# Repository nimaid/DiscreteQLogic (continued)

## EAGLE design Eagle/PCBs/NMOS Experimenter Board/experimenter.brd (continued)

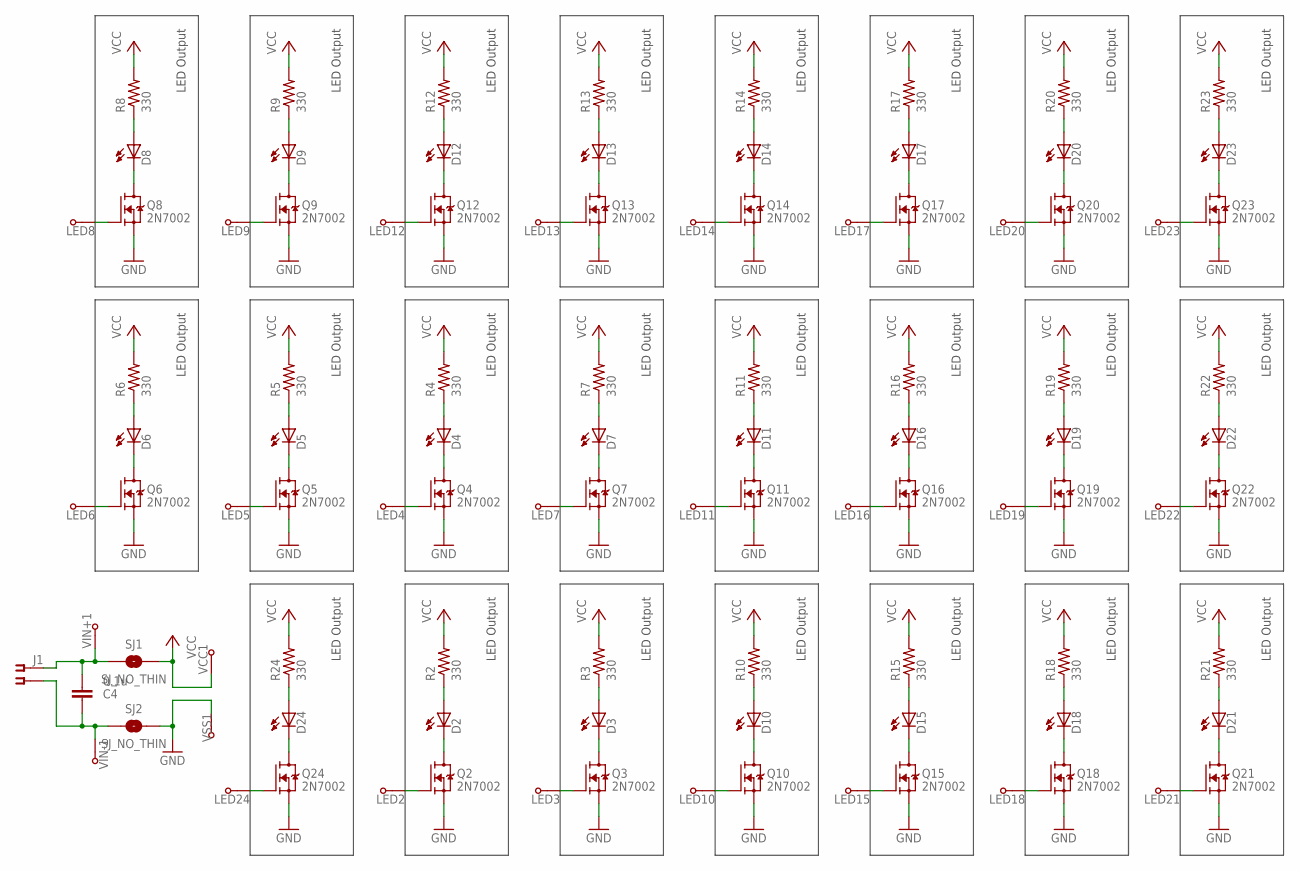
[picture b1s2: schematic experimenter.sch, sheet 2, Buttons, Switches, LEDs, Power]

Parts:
C4: 0.1u; C0603
D2, D3, D4, D5, D6, D7, D8, D9, D10, D11, D12, D13, D14, D15, D16, D17, D18, D19, D20, D21, D22, D23, D24: LED0603; CHIP-LED0603
J1: CON-F-2SCREWTERM-0.1"; OSTVN02A150
LED2, LED3, LED4, LED5, LED6, LED7, LED8, LED9, LED10, LED11, LED12, LED13, LED14, LED15, LED16, LED17, LED18, LED19, LED20, LED21, LED22, LED23, LED24: TPTHT; PROTOPAD-THT-PAD
Q2, Q3, Q4, Q5, Q6, Q7, Q8, Q9, Q10, Q11, Q12, Q13, Q14, Q15, Q16, Q17, Q18, Q19, Q20, Q21, Q22, Q23, Q24: 2N7002; SOT23
R2, R3, R4, R5, R6, R7, R8, R9, R10, R11, R12, R13, R14, R15, R16, R17, R18, R19, R20, R21, R22, R23, R24: 330; R0603
SJ1, SJ2: SJ_NO_THIN; SJ_2S-NO-THIN
VCC1: TPTHT; PROTOPAD-THT-PAD
VIN+1: TPTHT; PROTOPAD-THT-PAD
VIN-1: TPTHT; PROTOPAD-THT-PAD
VSS1: TPTHT; PROTOPAD-THT-PAD

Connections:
GND: Q2.2 (S), Q3.2 (S), Q4.2 (S), Q5.2 (S), Q6.2 (S), Q7.2 (S), Q8.2 (S), Q9.2 (S), Q10.2 (S), Q11.2 (S), Q12.2 (S), Q13.2 (S), Q14.2 (S), Q15.2 (S), Q16.2 (S), Q17.2 (S), Q18.2 (S), Q19.2 (S), Q20.2 (S), Q21.2 (S), Q22.2 (S), Q23.2 (S), Q24.2 (S), SJ2.2, VSS1.P1; also elsewhere on the board
unnamed: D10.A, R10.1
unnamed: LED10.P1, Q10.1 (G)
unnamed: D2.A, R2.1
unnamed: D10.C (K), Q10.3 (D)
unnamed: LED2.P1, Q2.1 (G)
unnamed: D2.C (K), Q2.3 (D)
unnamed: D3.A, R3.1
unnamed: LED3.P1, Q3.1 (G)
unnamed: D3.C (K), Q3.3 (D)
unnamed: D4.A, R4.1
unnamed: LED4.P1, Q4.1 (G)
unnamed: D4.C (K), Q4.3 (D)
unnamed: D5.A, R5.1
unnamed: LED5.P1, Q5.1 (G)
unnamed: D5.C (K), Q5.3 (D)
unnamed: D6.A, R6.1
unnamed: LED6.P1, Q6.1 (G)
unnamed: D6.C (K), Q6.3 (D)
unnamed: D7.A, R7.1
unnamed: LED7.P1, Q7.1 (G)
unnamed: D7.C (K), Q7.3 (D)
unnamed: D8.A, R8.1
unnamed: LED8.P1, Q8.1 (G)
unnamed: D8.C (K), Q8.3 (D)
unnamed: D9.A, R9.1
unnamed: LED9.P1, Q9.1 (G)
unnamed: D9.C (K), Q9.3 (D)
unnamed: D11.A, R11.1
unnamed: LED11.P1, Q11.1 (G)
unnamed: D11.C (K), Q11.3 (D)
unnamed: D12.A, R12.1
unnamed: LED12.P1, Q12.1 (G)
unnamed: D12.C (K), Q12.3 (D)
unnamed: D13.A, R13.1
unnamed: LED13.P1, Q13.1 (G)
unnamed: D13.C (K), Q13.3 (D)
unnamed: D14.A, R14.1
unnamed: LED14.P1, Q14.1 (G)
unnamed: D14.C (K), Q14.3 (D)
unnamed: D15.A, R15.1
unnamed: LED15.P1, Q15.1 (G)
unnamed: D15.C (K), Q15.3 (D)
unnamed: D16.A, R16.1
unnamed: LED16.P1, Q16.1 (G)
unnamed: D16.C (K), Q16.3 (D)
unnamed: D17.A, R17.1
unnamed: LED17.P1, Q17.1 (G)
unnamed: D17.C (K), Q17.3 (D)
unnamed: D18.A, R18.1
unnamed: LED18.P1, Q18.1 (G)
unnamed: D18.C (K), Q18.3 (D)
unnamed: D19.A, R19.1
unnamed: LED19.P1, Q19.1 (G)
unnamed: D19.C (K), Q19.3 (D)
unnamed: D20.A, R20.1
unnamed: LED20.P1, Q20.1 (G)
unnamed: D20.C (K), Q20.3 (D)
unnamed: D21.A, R21.1
unnamed: LED21.P1, Q21.1 (G)
unnamed: D21.C (K), Q21.3 (D)
unnamed: D22.A, R22.1
unnamed: LED22.P1, Q22.1 (G)
unnamed: D22.C (K), Q22.3 (D)
unnamed: D23.A, R23.1
unnamed: LED23.P1, Q23.1 (G)
unnamed: D23.C (K), Q23.3 (D)
unnamed: D24.A, R24.1
unnamed: LED24.P1, Q24.1 (G)
unnamed: D24.C (K), Q24.3 (D)
unnamed: C4.1, J1.P$2 (S1), SJ2.1, VIN-1.P1
unnamed: C4.2, J1.P$1 (S), SJ1.1, VIN+1.P1
VCC: R2.2, R3.2, R4.2, R5.2, R6.2, R7.2, R8.2, R9.2, R10.2, R11.2, R12.2, R13.2, R14.2, R15.2, R16.2, R17.2, R18.2, R19.2, R20.2, R21.2, R22.2, R23.2, R24.2, SJ1.2, VCC1.P1; also elsewhere on the board

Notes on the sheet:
LED Output

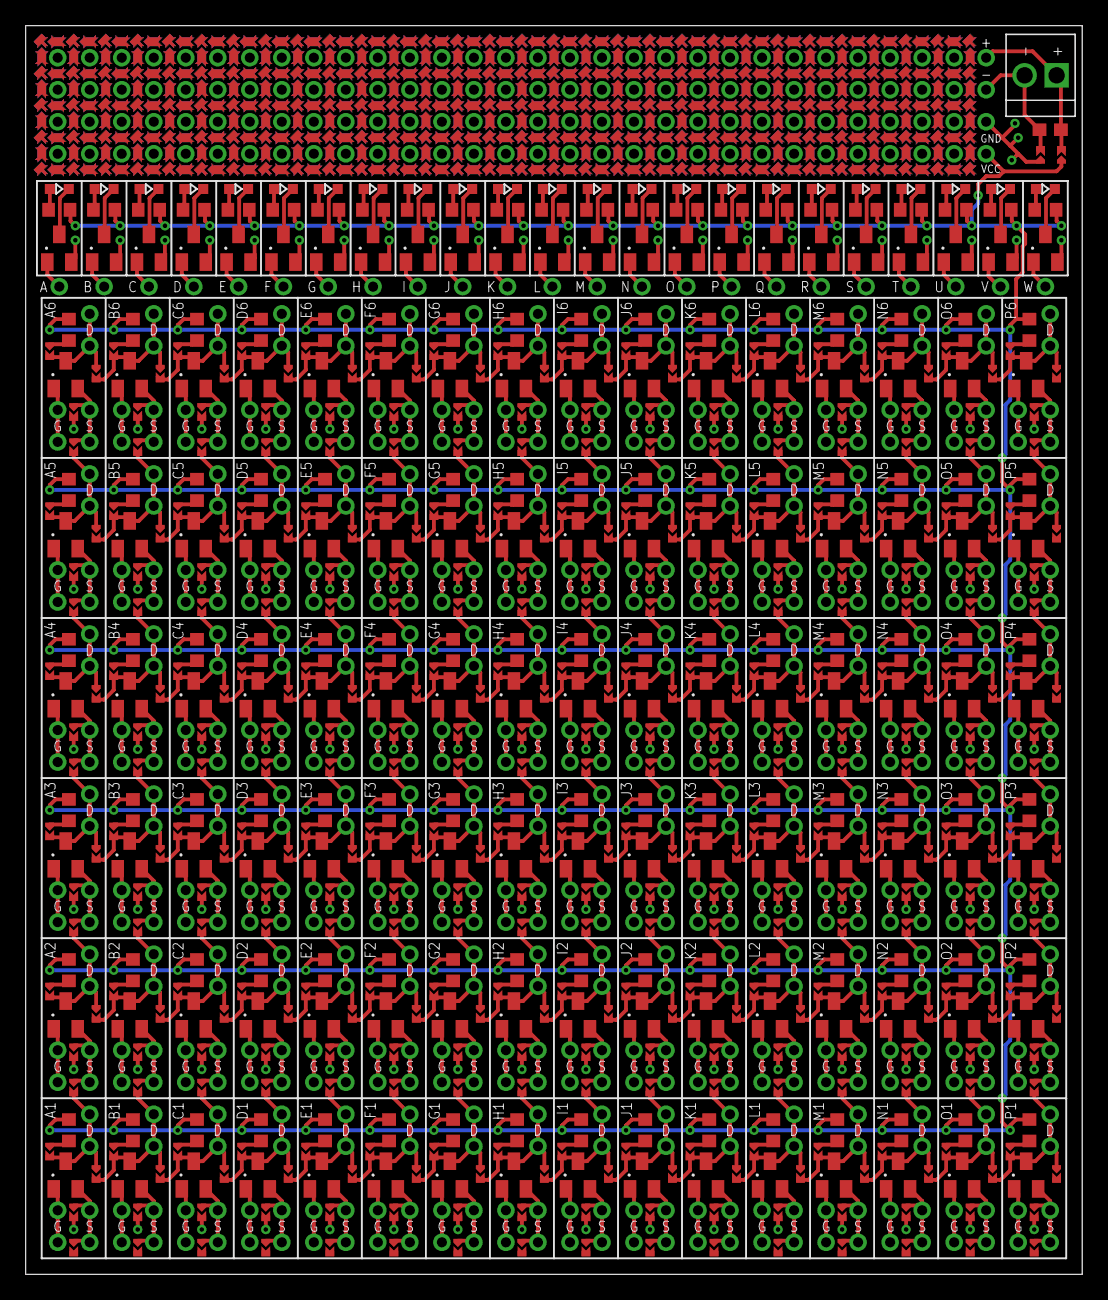
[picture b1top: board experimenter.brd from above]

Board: 2 copper layers, 83.8 x 99.1 mm, 1783 parts (0 on the bottom side), 457 nets.

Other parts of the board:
U$1, U$9, U$13, U$17, U$21, U$25, U$29, U$33, U$65, U$69, U$73, U$77, U$97, U$101, U$105, U$109, U$113, U$117, U$121, U$125, U$129, U$133, U$137, U$141, U$145, U$149, U$153, U$157, U$161, U$165, U$169, U$173, U$177, U$181, U$185, U$189, U$193, U$197, U$201, U$205, U$209, U$213, U$217, U$221, U$225, U$229, U$233, U$237, U$241, U$245, U$249, U$253, U$257, U$261, U$265, U$269, U$273, U$277, U$281, U$285, U$289, U$293, U$297, U$301, U$305, U$309, U$313, U$317, U$321, U$325, U$329, U$333, U$337, U$341, U$345, U$349, U$353, U$357, U$361, U$365, U$369, U$373, U$377, U$381, U$385, U$389, U$393, U$397, U$401, U$405, U$409, U$413, U$417, U$421, U$425, U$429, U$433, U$437, U$441, U$445, U$449, U$453, U$457, U$461, U$465, U$469, U$473, U$477, U$481, U$485, U$489, U$493, U$497, U$501, U$505, U$509: PROTOPADTHT; PROTOPAD-THT
U$2, U$3, U$5, U$7, U$10, U$11, U$14, U$15, U$18, U$19, U$22, U$23, U$26, U$27, U$30, U$31, U$34, U$35, U$37, U$39, U$41, U$43, U$45, U$47, U$49, U$51, U$53, U$55, U$57, U$59, U$61, U$63, U$66, U$67, U$70, U$71, U$74, U$75, U$78, U$79, U$81, U$83, U$85, U$87, U$89, U$91, U$93, U$95, U$98, U$99, U$102, U$103, U$106, U$107, U$110, U$111, U$114, U$115, U$118, U$119, U$122, U$123, U$126, U$127, U$130, U$131, U$134, U$135, U$138, U$139, U$142, U$143, U$146, U$147, U$150, U$151, U$154, U$155, U$158, U$159, U$162, U$163, U$166, U$167, U$170, U$171, U$174, U$175, U$178, U$179, U$182, U$183, U$186, U$187, U$190, U$191, U$194, U$195, U$198, U$199, U$202, U$203, U$206, U$207, U$210, U$211, U$214, U$215, U$218, U$219, U$222, U$223, U$226, U$227, U$230, U$231, U$234, U$235, U$238, U$239, U$242, U$243, U$246, U$247, U$250, U$251, U$254, U$255, U$258, U$259, U$262, U$263, U$266, U$267, U$270, U$271, U$274, U$275, U$278, U$279, U$282, U$283, U$286, U$287, U$290, U$291, U$294, U$295, U$298, U$299, U$302, U$303, U$306, U$307, U$310, U$311, U$314, U$315, U$318, U$319, U$322, U$323, U$326, U$327, U$330, U$331, U$334, U$335, U$338, U$339, U$342, U$343, U$346, U$347, U$350, U$351, U$354, U$355, U$358, U$359, U$362, U$363, U$366, U$367, U$370, U$371, U$374, U$375, U$378, U$379, U$382, U$383, U$386, U$387, U$390, U$391, U$394, U$395, U$398, U$399, U$402, U$403, U$406, U$407, U$410, U$411, U$414, U$415, U$418, U$419, U$422, U$423, U$426, U$427, U$430, U$431, U$434, U$435, U$438, U$439, U$442, U$443, U$446, U$447, U$450, U$451, U$454, U$455, U$458, U$459, U$462, U$463, U$466, U$467, U$470, U$471, U$474, U$475, U$478, U$479, U$482, U$483, U$486, U$487, U$490, U$491, U$494, U$495, U$498, U$499, U$502, U$503, U$506, U$507, U$510, U$511, U$513, U$515, U$517, U$519, U$521, U$523, U$525, U$527, U$529: PROTOPAD-BETWEEN
U$4, U$6, U$8, U$12, U$16, U$20, U$24, U$28, U$32, U$36, U$38, U$40, U$42, U$44, U$46, U$48, U$50, U$52, U$54, U$56, U$58, U$60, U$62, U$64, U$68, U$72, U$76, U$80, U$82, U$84, U$86, U$88, U$90, U$92, U$94, U$96, U$100, U$104, U$108, U$112, U$116, U$120, U$124, U$128, U$132, U$136, U$140, U$144, U$148, U$152, U$156, U$160, U$164, U$168, U$172, U$176, U$180, U$184, U$188, U$192, U$196, U$200, U$204, U$208, U$212, U$216, U$220, U$224, U$228, U$232, U$236, U$240, U$244, U$248, U$252, U$256, U$260, U$264, U$268, U$272, U$276, U$280, U$284, U$288, U$292, U$296, U$300, U$304, U$308, U$312, U$316, U$320, U$324, U$328, U$332, U$336, U$340, U$344, U$348, U$352, U$356, U$360, U$364, U$368, U$372, U$376, U$380, U$384, U$388, U$392, U$396, U$400, U$404, U$408, U$412, U$416, U$420, U$424, U$428, U$432, U$436, U$440, U$444, U$448, U$452, U$456, U$460, U$464, U$468, U$472, U$476, U$480, U$484, U$488, U$492, U$496, U$500, U$504, U$508, U$512, U$514, U$516, U$518, U$520, U$522, U$524, U$526, U$528, U$530, U$531: PROTOPAD-CENTER

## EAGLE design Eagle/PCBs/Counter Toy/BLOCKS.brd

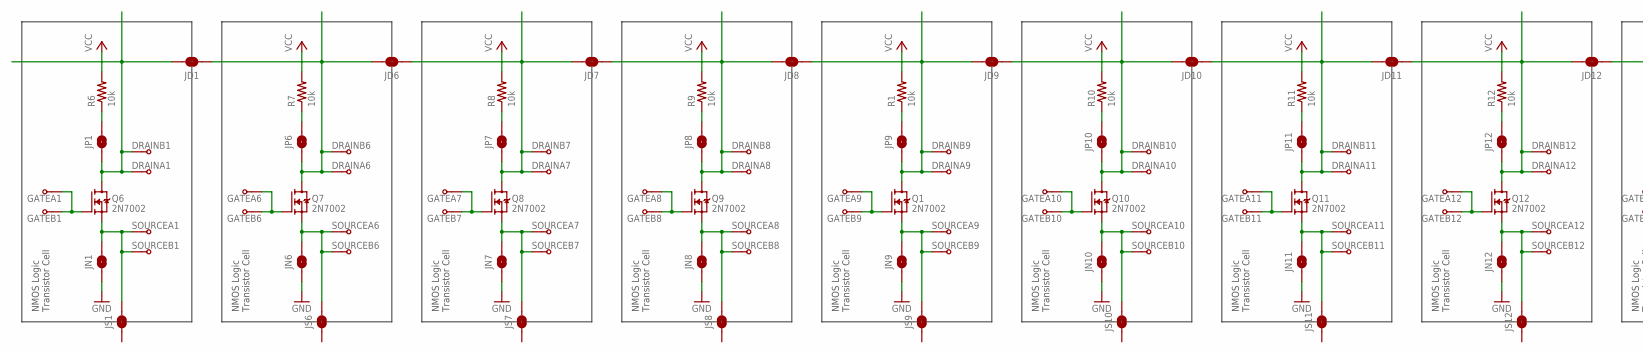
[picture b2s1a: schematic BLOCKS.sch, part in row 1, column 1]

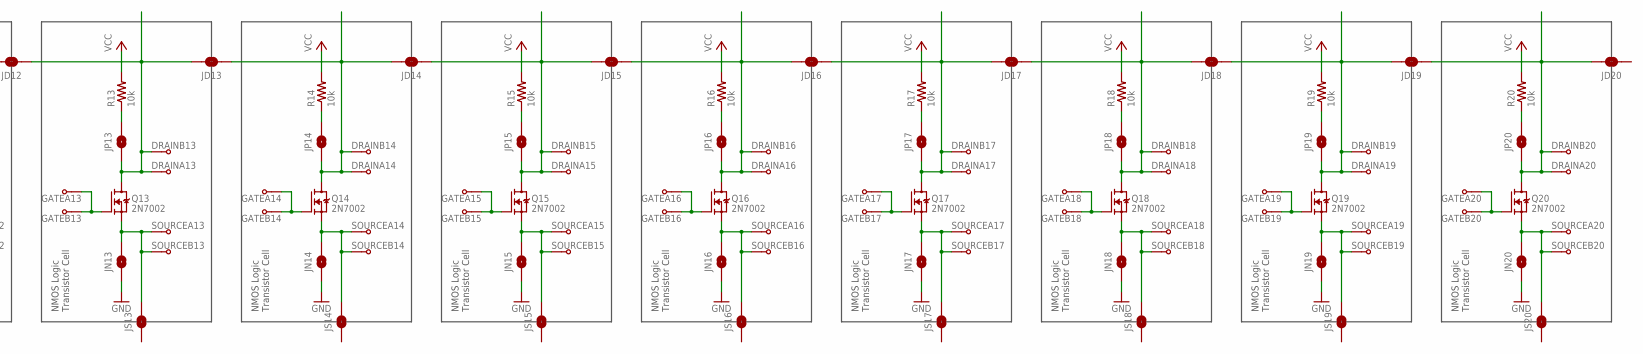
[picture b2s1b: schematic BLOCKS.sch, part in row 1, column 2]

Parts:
DRAINA1, DRAINA6, DRAINA7, DRAINA8, DRAINA9, DRAINA10, DRAINA11, DRAINA12, DRAINA13, DRAINA14, DRAINA15, DRAINA16, DRAINA17, DRAINA18, DRAINA19, DRAINA20: TPTHT; PROTOPAD-THT-PAD
DRAINB1, DRAINB6, DRAINB7, DRAINB8, DRAINB9, DRAINB10, DRAINB11, DRAINB12, DRAINB13, DRAINB14, DRAINB15, DRAINB16, DRAINB17, DRAINB18, DRAINB19, DRAINB20: TPTHT; PROTOPAD-THT-PAD
GATEA1, GATEA6, GATEA7, GATEA8, GATEA9, GATEA10, GATEA11, GATEA12, GATEA13, GATEA14, GATEA15, GATEA16, GATEA17, GATEA18, GATEA19, GATEA20: TPTHT; PROTOPAD-THT-PAD
GATEB1, GATEB6, GATEB7, GATEB8, GATEB9, GATEB10, GATEB11, GATEB12, GATEB13, GATEB14, GATEB15, GATEB16, GATEB17, GATEB18, GATEB19, GATEB20: TPTHT; PROTOPAD-THT-PAD
JD1, JD6, JD7, JD8, JD9, JD10, JD11, JD12, JD13, JD14, JD15, JD16, JD17, JD18, JD19, JD20: SJ_NO_THIN; SJ_2S-NO-THIN
JN1, JN6, JN7, JN8, JN9, JN10, JN11, JN12, JN13, JN14, JN15, JN16, JN17, JN18, JN19, JN20: SJ_NO_THIN; SJ_2S-NO-THIN
JP1, JP6, JP7, JP8, JP9, JP10, JP11, JP12, JP13, JP14, JP15, JP16, JP17, JP18, JP19, JP20: SJ_NO_THIN; SJ_2S-NO-THIN
JS1, JS6, JS7, JS8, JS9, JS10, JS11, JS12, JS13, JS14, JS15, JS16, JS17, JS18, JS19, JS20: SJ_NO_THIN; SJ_2S-NO-THIN
Q1, Q6, Q7, Q8, Q9, Q10, Q11, Q12, Q13, Q14, Q15, Q16, Q17, Q18, Q19, Q20: 2N7002; SOT23
R1, R6, R7, R8, R9, R10, R11, R12, R13, R14, R15, R16, R17, R18, R19, R20: 10k; R0603
SOURCEA1, SOURCEA6, SOURCEA7, SOURCEA8, SOURCEA9, SOURCEA10, SOURCEA11, SOURCEA12, SOURCEA13, SOURCEA14, SOURCEA15, SOURCEA16, SOURCEA17, SOURCEA18, SOURCEA19, SOURCEA20: TPTHT; PROTOPAD-THT-PAD
SOURCEB1, SOURCEB6, SOURCEB7, SOURCEB8, SOURCEB9, SOURCEB10, SOURCEB11, SOURCEB12, SOURCEB13, SOURCEB14, SOURCEB15, SOURCEB16, SOURCEB17, SOURCEB18, SOURCEB19, SOURCEB20: TPTHT; PROTOPAD-THT-PAD

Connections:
GND: JN1.1, JN6.1, JN7.1, JN8.1, JN9.1, JN10.1, JN11.1, JN12.1, JN13.1, JN14.1, JN15.1, JN16.1, JN17.1, JN18.1, JN19.1, JN20.1
unnamed: JP9.2, R1.1
unnamed: JN9.2, JS9.2, Q1.2 (S), SOURCEA9.P1, SOURCEB9.P1
unnamed: DRAINA9.P1, DRAINB9.P1, JD8.1, JD9.2, JP9.1, Q1.3 (D)
unnamed: JP1.2, R6.1
unnamed: JN1.2, JS1.2, Q6.2 (S), SOURCEA1.P1, SOURCEB1.P1
unnamed: DRAINA1.P1, DRAINB1.P1, JD1.2, JP1.1, Q6.3 (D)
unnamed: GATEA1.P1, GATEB1.P1, Q6.1 (G)
unnamed: JP6.2, R7.1
unnamed: JN6.2, JS6.2, Q7.2 (S), SOURCEA6.P1, SOURCEB6.P1
unnamed: DRAINA6.P1, DRAINB6.P1, JD1.1, JD6.2, JP6.1, Q7.3 (D)
unnamed: GATEA6.P1, GATEB6.P1, Q7.1 (G)
unnamed: JP7.2, R8.1
unnamed: JN7.2, JS7.2, Q8.2 (S), SOURCEA7.P1, SOURCEB7.P1
unnamed: DRAINA7.P1, DRAINB7.P1, JD6.1, JD7.2, JP7.1, Q8.3 (D)
unnamed: GATEA7.P1, GATEB7.P1, Q8.1 (G)
unnamed: JP8.2, R9.1
unnamed: JN8.2, JS8.2, Q9.2 (S), SOURCEA8.P1, SOURCEB8.P1
unnamed: DRAINA8.P1, DRAINB8.P1, JD7.1, JD8.2, JP8.1, Q9.3 (D)
unnamed: GATEA8.P1, GATEB8.P1, Q9.1 (G)
unnamed: GATEA9.P1, GATEB9.P1, Q1.1 (G)
unnamed: JP10.2, R10.1
unnamed: JN10.2, JS10.2, Q10.2 (S), SOURCEA10.P1, SOURCEB10.P1
unnamed: DRAINA10.P1, DRAINB10.P1, JD9.1, JD10.2, JP10.1, Q10.3 (D)
unnamed: GATEA10.P1, GATEB10.P1, Q10.1 (G)
unnamed: JP11.2, R11.1
unnamed: JN11.2, JS11.2, Q11.2 (S), SOURCEA11.P1, SOURCEB11.P1
unnamed: DRAINA11.P1, DRAINB11.P1, JD10.1, JD11.2, JP11.1, Q11.3 (D)
unnamed: GATEA11.P1, GATEB11.P1, Q11.1 (G)
unnamed: JP12.2, R12.1
unnamed: JN12.2, JS12.2, Q12.2 (S), SOURCEA12.P1, SOURCEB12.P1
unnamed: DRAINA12.P1, DRAINB12.P1, JD11.1, JD12.2, JP12.1, Q12.3 (D)
unnamed: GATEA12.P1, GATEB12.P1, Q12.1 (G)
unnamed: JP13.2, R13.1
unnamed: JN13.2, JS13.2, Q13.2 (S), SOURCEA13.P1, SOURCEB13.P1
unnamed: DRAINA13.P1, DRAINB13.P1, JD12.1, JD13.2, JP13.1, Q13.3 (D)
unnamed: GATEA13.P1, GATEB13.P1, Q13.1 (G)
unnamed: JP14.2, R14.1
unnamed: JN14.2, JS14.2, Q14.2 (S), SOURCEA14.P1, SOURCEB14.P1
unnamed: DRAINA14.P1, DRAINB14.P1, JD13.1, JD14.2, JP14.1, Q14.3 (D)
unnamed: GATEA14.P1, GATEB14.P1, Q14.1 (G)
unnamed: JP15.2, R15.1
unnamed: JN15.2, JS15.2, Q15.2 (S), SOURCEA15.P1, SOURCEB15.P1
unnamed: DRAINA15.P1, DRAINB15.P1, JD14.1, JD15.2, JP15.1, Q15.3 (D)
unnamed: GATEA15.P1, GATEB15.P1, Q15.1 (G)
unnamed: JP16.2, R16.1
unnamed: JN16.2, JS16.2, Q16.2 (S), SOURCEA16.P1, SOURCEB16.P1
unnamed: DRAINA16.P1, DRAINB16.P1, JD15.1, JD16.2, JP16.1, Q16.3 (D)
unnamed: GATEA16.P1, GATEB16.P1, Q16.1 (G)
unnamed: JP17.2, R17.1
unnamed: JN17.2, JS17.2, Q17.2 (S), SOURCEA17.P1, SOURCEB17.P1
unnamed: DRAINA17.P1, DRAINB17.P1, JD16.1, JD17.2, JP17.1, Q17.3 (D)
unnamed: GATEA17.P1, GATEB17.P1, Q17.1 (G)
unnamed: JP18.2, R18.1
unnamed: JN18.2, JS18.2, Q18.2 (S), SOURCEA18.P1, SOURCEB18.P1
unnamed: DRAINA18.P1, DRAINB18.P1, JD17.1, JD18.2, JP18.1, Q18.3 (D)
unnamed: GATEA18.P1, GATEB18.P1, Q18.1 (G)
unnamed: JP19.2, R19.1
unnamed: JN19.2, JS19.2, Q19.2 (S), SOURCEA19.P1, SOURCEB19.P1
unnamed: DRAINA19.P1, DRAINB19.P1, JD18.1, JD19.2, JP19.1, Q19.3 (D)
unnamed: GATEA19.P1, GATEB19.P1, Q19.1 (G)
unnamed: JP20.2, R20.1
unnamed: JN20.2, JS20.2, Q20.2 (S), SOURCEA20.P1, SOURCEB20.P1
unnamed: DRAINA20.P1, DRAINB20.P1, JD19.1, JD20.2, JP20.1, Q20.3 (D)
unnamed: GATEA20.P1, GATEB20.P1, Q20.1 (G)
VCC: R1.2, R6.2, R7.2, R8.2, R9.2, R10.2, R11.2, R12.2, R13.2, R14.2, R15.2, R16.2, R17.2, R18.2, R19.2, R20.2

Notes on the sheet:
NMOS Logic Transistor Cell

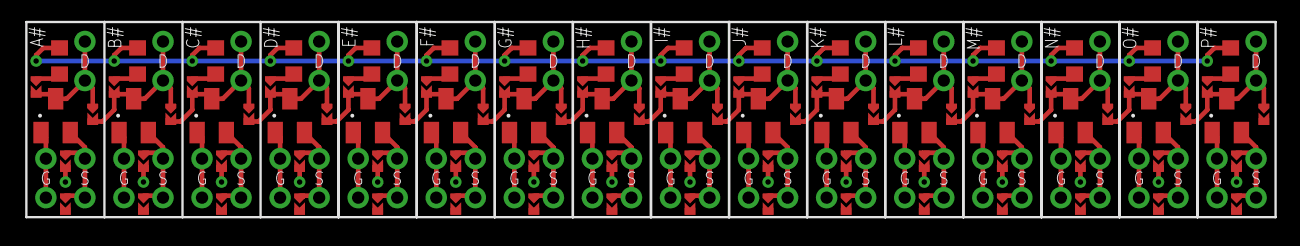
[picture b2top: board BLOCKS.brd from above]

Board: 2 copper layers, 192 parts (0 on the bottom side), 66 nets.

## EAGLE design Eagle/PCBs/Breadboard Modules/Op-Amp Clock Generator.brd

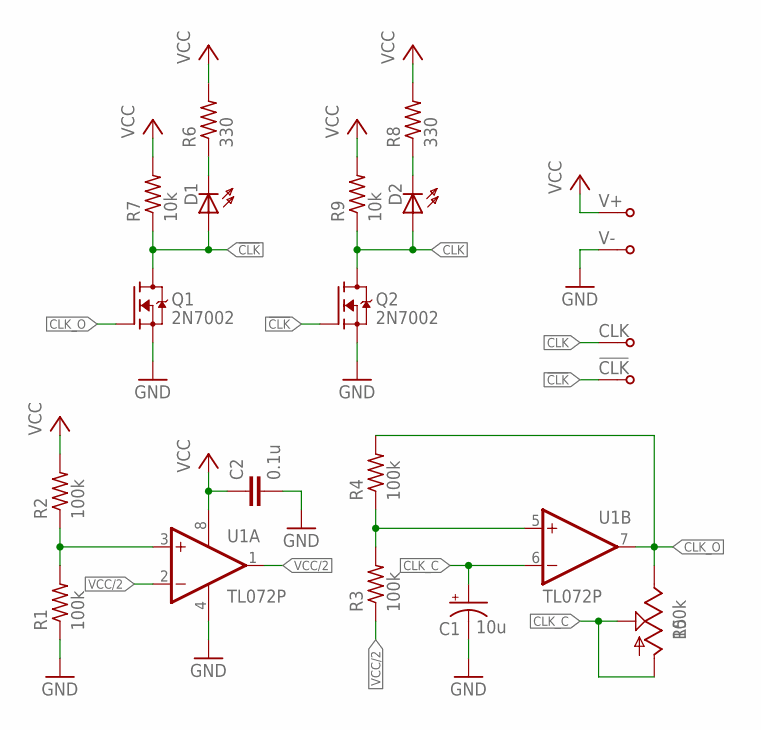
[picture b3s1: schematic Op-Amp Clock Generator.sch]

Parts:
!CLK: TPTHT; PROTOPAD-THT-PAD
C1: 10u; TT2D5
C2: 0.1u; C0603
CLK: TPTHT; PROTOPAD-THT-PAD
D1, D2: LED0603; CHIP-LED0603
Q1, Q2: 2N7002; SOT23
R1, R2, R3, R4: 100k; R0603
R5: 100k; ALPHA_POT_VERTICAL
R6, R8: 330; R0603
R7, R9: 10k; R0603
U1: TL072P; DIL08
V+: TPTHT; PROTOPAD-THT-PAD
V-: TPTHT; PROTOPAD-THT-PAD

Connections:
!CLK: !CLK.P1, D1.A, Q1.3 (D), Q2.1 (G), R7.1
CLK: CLK.P1, D2.A, Q2.3 (D), R9.1
CLK_C: C1.+, R5.P$2 (S), R5.P$3 (A), U1.6 (-IN)
CLK_O: Q1.1 (G), R4.2, R5.P$1 (E), U1.7 (OUT)
GND: C1.-, C2.2, Q1.2 (S), Q2.2 (S), R1.1, U1.4 (V-), V-.P1
unnamed: R1.2, R2.1, U1.3 (+IN)
unnamed: R3.2, R4.1, U1.5 (+IN)
unnamed: D1.C (K), R6.1
unnamed: D2.C (K), R8.1
VCC: C2.1, R2.2, R6.2, R7.2, R8.2, R9.2, U1.8 (V+), V+.P1
VCC/2: R3.1, U1.1 (OUT), U1.2 (-IN)

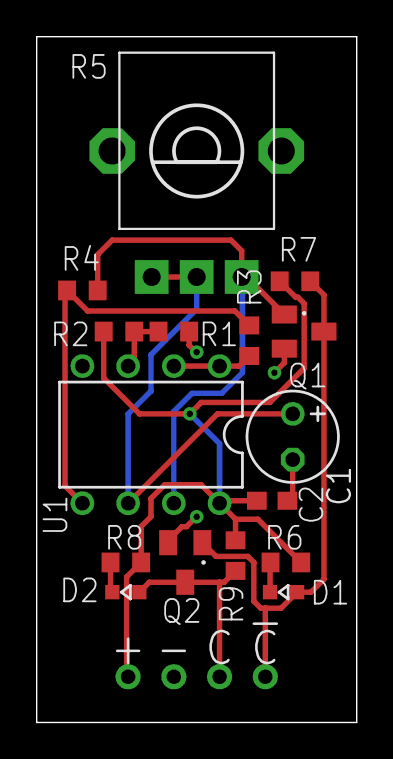
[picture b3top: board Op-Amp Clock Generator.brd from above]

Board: 2 copper layers, 17.8 x 38.1 mm, 20 parts (0 on the bottom side), 11 nets.

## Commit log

2023-04-15 Add initial NMOS components
2023-04-15 refactor
2023-04-15 Added RAM to toy
2023-04-16 Added ROM and PC
2023-04-16 Goodbye pretty 4-nand XOR, here's a better NMOS one with 6Q 3R
    The symmetrical 4 nand gate "diamond" took 8Q 4R, so we save 2Q and 1R.
2023-04-16 Cleaned up XOR (it was using an AOI2-2 lol)
2023-04-16 Optimized "zero" control bit for ALU inputs
2023-04-16 Counter upgrades
2023-04-16 Made a counter toy design to do a full proof of concept with
2023-04-17 Started LTspice sims
2023-04-17 Got first gate working
2023-04-17 Added clock
2023-04-17 NAND
2023-04-17 Added AOI2x2, XOR
2023-04-17 XNOR
2023-04-17 OR gate
2023-04-17 AND gate
2023-04-17 Cleaned up parts
2023-04-17 Add enabler
2023-04-17 Updated enable symbol
2023-04-17 Cleaned up component layouts
2023-04-17 Added pictures for NMOS basics
2023-04-17 Started work on readme
2023-04-17 AOI gates
2023-04-17 Updated mux
2023-04-18 Demultiplexer
2023-04-18 Made names lowercase
2023-04-18 Fixed file names
2023-04-18 Fixed uppercase filenames
2023-04-18 Started work on Eagle design blocks
2023-04-18 Moe design blocks
2023-04-19 Made DFF and byte more compact
2023-04-19 Much better enabler
2023-04-19 Optimized enabler with inversion
2023-04-19 Inverted enabler
2023-04-19 Made a button input and a multiplexer
2023-04-19 Trying comparator, failing
2023-04-19 Added button input with hysteresis
2023-04-19 Gave in and used a read schmitt trigger on my buttons
2023-04-20 Optimized reset and mux with inversions
    No single not gates
2023-04-20 Better DFF
2023-04-20 Simpler architecture that uses ALU to inc PC
2023-04-20 Simplified DFF to JK-based
2023-04-20 TFF (with race...)
    Computers are hard...
2023-04-20 Placeholder TFF and a PC
2023-04-20 DFF revert
2023-04-20 Generalized DFF
2023-04-20 THOSE WERE BAD DFFs!
    TFF is also now DFF based to prevent race.
2023-04-20 Removed outdated images
2023-04-20 Fixed name
2023-04-20 SO MUCH GOOD INFO
2023-04-20 Helpful diagrams for deconstructing the DFF
2023-04-20 Made syn. version of counter, no ripple.
    More stable for use as a PC, but more transistors.
2023-04-21 Fixed AOI naming
2023-04-21 Cleaned up inverted enabler
2023-04-21 Made DFFs modular (from SR latches)
2023-04-21 Updates SR to have both NAND and NOR versions.
2023-04-21 OH, named RS and SR, silly me
2023-04-21 Start work on latches
2023-04-21 Fixed naming
    I remembered to use `git mv` to avoid the end of the world! :D
2023-04-21 First version of latches / DFF
2023-04-21 Added reset-only DFF
2023-04-21 Start MUX and DMUX
2023-04-21 Fixed mux/dmux
2023-04-21 better mux
2023-04-21 Simplified ALU, added conditional decoder
2023-04-23 Testing open collector setup
2023-04-23 Update packages
2023-04-23 A 6x12 grid fits
2023-04-23 Removed useless jumpers
2023-04-23 Added 6x buttons with debouncing
2023-04-23 Added basic power and stripboard
2023-04-23 Added switches, preemptive first version
2023-04-24 Made crossing wires cleaner
2023-04-24 Made simple 4-bit counter that can fit on the 72-transistor lab board
2023-04-24 Added amazing protoboard area.
    https://www.eevblog.com/forum/manufacture/improved-protoboardperfboard-for-direct-soic-mounting/
2023-04-25 Drastically lowered part count
    * D-latches instead of edge-triggered flip-flops
    * Common pulldown open drain enablers
2023-04-25 Start rework on experimenter
2023-04-25 Removed LED
2023-04-25 Create LED output
2023-04-25 Fixed duplicate names?
2023-04-25 Wow, 92 transistors and 8 LEDs
2023-04-25 Better power distribution
2023-04-25 Fixed power input connector
2023-04-25 Added startup circuit!
    Not so bad lol, who needs reset lines?
2023-04-25 Simplified startup circuit
2023-04-25 Lots of changes
2023-04-27 ALU simplifications, proper PC
2023-04-27 Simplifiied experiment board
2023-04-27 Started emulator with the FET-80 ALU
2023-04-27 Eagle v1 done
2023-04-27 Started attempt to make board in KiCad
2023-04-28 Better multiplexer, used pre-inverted output
2023-04-28 Simplified PC by sharing NOT gate on D input to TFF
2023-04-28 NMOS-based schmitt inverter
2023-04-28 Simplified XNOR with OAI gate, made inverted inverter with it
2023-04-28 Realised the input/output inverters could be replaced with NAND and multiple cycles, lol
    This went from the HACK ALU to almost the MyNOR "ALU". Just an adder, an 8 channel NAND gate, and a multiplexer! The NAND is a free additional output from the adder, too! (It also has AND and XOR out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
2023-04-28 Added schmitt inverter to LTspice
2023-04-29 Wow, a full adder gives free XOR, AND. NAND, and NOR
    How generous. I call it an Adder+, and it plus a multiplexer is my ALU now.
2023-04-29 Started work on first abstract implimentation of the machine code
2023-04-30 Added registers RAM to the emulator
2023-04-30 Copied some of my work from NAND2Tetris for the parser
2023-04-30 Symbol parsing
2023-04-30 Finished symbol extracting
2023-04-30 Finished basic assembly parser
2023-04-30 Almost done with the assembler.
2023-04-30 Basic symbolic assembler done
2023-04-30 Using @ to denote implicit use of MEM
2023-04-30 UPPER
2023-04-30 Allowed MEM to access non-direct values
2023-04-30 Indirect memory addressing works
2023-04-30 Finished program ROM
2023-04-30 Fixed direct values in dest
2023-04-30 Added multi-level pointers
2023-04-30 Added way to view preprocessed assembly
2023-04-30 Remapped IO to be more efficient
2023-04-30 Refactored to separate files
2023-04-30 Better practices when programming pointers
2023-04-30 better formatting
2023-04-30 Added class for FET-80 system
2023-04-30 Added required methods to FET-80
2023-04-30 spacing
2023-04-30 Generalized symbol table constants
2023-04-30 Rename file extension
2023-04-30 More parameter generalizations
2023-04-30 Begin Emulator class
2023-04-30 Added basic emulation!
2023-04-30 Cleaned up structure of assembler
2023-04-30 Fixed bug in assembly code!
    I know it's a bug because MY EMULATOR WORKS!
2023-04-30 Added human-readable assembly methods
2023-04-30 Start work on TKinter GIU
2023-05-01 Transfer FET-80 stuff to new repo
2023-05-02 101 transistors for a hex decoder!
2023-05-03 Did the math, got the 7-segment hex decoder to 88Q
2023-05-03 Yup, 88Q. And now I have mastered NMOS boolean expressions.
2023-05-03 Started experiments with sub-gate level design optimizations
2023-05-04 Started restructuring Digital circuits
2023-05-04 Rename and multiple NAND/NOT/NOR
2023-05-04 SR and RS latches
2023-05-04 Added gated D latch
    Using fancy compound NAND circuits
2023-05-04 Better D latch for NMOS
2023-05-04 Renamed minimal SR latch
2023-05-04 Added DFF and TFF variants
    1 transistor can pull the reset lines down. I made versions with integrated pull-downs for each flop, and ones with the pull-downs missing for use with a single shared pull-down.
2023-05-04 Made pd mean "Has pull-down transistor on set/reset line"
2023-05-04 That isn't a viable method sadly, logic oscillates
2023-05-04 Added Schmitt trigger inverter (does not work in Digital)
2023-05-05 Binary Clock
2023-05-05 Updated sexagesimal clock
2023-05-05 Made better sexagesimal versions with color coded LEDs
2023-05-05 Started work on BCD clock
2023-05-05 Mock-up of colored light idea
2023-05-05 Much nicer layout
    I'm probably gonna use the H:M:S one, because a 1 Hz signal is a simple CD4060, 32.768 kHz crystal, and a basic 13Q6R TFF away. Plus, more blinkenlights.
2023-05-05 Added DFF to LTspice
2023-05-05 Renamed LTspice models
2023-05-05 Resettable DFF
2023-05-05 Moved images and documents around
2023-05-12 Simplified input AND reduced transistors
2023-05-12 Clock generator module
2023-05-19 kicad start
2023-05-19 op amp clock
2023-05-19 Started clock simulator
2023-05-22 Holy shit, I opened my third eye and halved the transistors (187)
2023-05-22 Okay, that broke my sim
2023-05-22 Okay, these work in my sim
2023-05-22 More optimizations
2023-05-22 Better layout
2023-05-22 New pictures
